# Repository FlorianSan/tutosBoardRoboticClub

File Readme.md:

# Carte tutos club Robot

Carte électronique pour apprendre les bases de l'électronique et de la programmation au nouveaux membres du club robotique.

Cette carte devrait être suffisamment compacte et pratique pour être emportée chez soi.

Sujets:

+ LEDs
+ boutons, pullups, ...
+ potentiomètre: analogique
+ PWM
+ UART
+ I2C
+ Encoder
+ Asservissement d'un moteur

Carte compatible Nucleo F411, F401RE. (et peut-être d'autres)

# Getting started

Le plus simple pour démarrer est d'installer VSCode, et l'extension PlateformIO.

Créer un projet pour la carte que vous utilisez (par exemple : ST Nucleo F401RE), avec le framwork Arduino.

Ajouter ceci au fichier `platformio.ini` pour activer l'UART6 qui va permettre de communiquer avec l'ATtiny1616 :

`build_flags = -D ENABLE_HWSERIAL6`

# Pinout

## Nucleo

| Pin | Signal    |
|-----|-----------|
|PA0  |BTN1 (B1)  |
|PA1  |BTN2 (B2)  |
|PA4  |BUZZ       |
|PA8  |Enc1A      |
|PA9  |Enc1B      |
|PA10 |Display_CLK|
|PA11 |UART6_TX   |
|PA12 |UART6_RX   |
|PA15 |MotB       |
|PB0  |POT        |
|PB1  |LED1       |
|PB4  |SERVO1     |
|PB5  |SERVO2     |
|PB6  |Enc2A      |
|PB7  |Enc2B      |
|PB8  |SCL1       |
|PB9  |SDA1       |
|PB10 |MotA       |
|PB12 |Attiny_link|
|PC4  |Display_DIO|
|PC8  |LED2       |
|PC9  |INT_TCA    |

Les jumpers JP1 et JP2 connectent respectivement une résistance de pullup et de pulldown aux signaux BTN1 et BTN2.

Afin d'utiliser les servomoteurs ou le moteur, il faut alimenter la carte par le connecteur jack DC en 12V (12V sur le connecteur central, GND sur l'extérieur), et régler le jumper JP5 de la nucleo (à côté du bouton RESET) sur "E5V".
La led D19 devrait s'allumer.

## TCA9554

| Pin | Signal  |
|-----|---------|
|P0   |D4       |
|P1   |D5       |
|P2   |D6       |
|P3   |D7       |
|P4   |D17      |
|P5   |D18      |
|P6   |SW6 (B3) |
|P7   |SW7 (B4) |

SW5 permet de régler un bit d'adresse (A0).

SW4 permet de connecter ou pas les pullups sur SDA et SCL.

La broche INT est connectée sur la broche PC9 de la nucleo.

Les broches d'adresses A1 et A2 sont connectés à GND.

datasheet : [http://www.ti.com/lit/ds/symlink/tca9554.pdf](http://www.ti.com/lit/ds/symlink/tca9554.pdf)

## Display

L'afficheur 7segments 4 digits est commandé par un TM1637.

datasheet : [https://www.mcielectronics.cl/website_MCI/static/documents/Datasheet_TM1637.pdf](https://www.mcielectronics.cl/website_MCI/static/documents/Datasheet_TM1637.pdf)

## Driver moteur

Le driver moteur est un BD62120AEFJ.

datasheet : [https://docs.rs-online.com/a300/0900766b816747fb.pdf](https://docs.rs-online.com/a300/0900766b816747fb.pdf)

## ATtiny 1616

:warning: Si vous regardez ça, vous savez ce que vous faites !

| Pin | Signal    |
|-----|-----------|
|PA0  |UPDI       |
|PA2  |Attiny_link|
|PA4  |D10        |
|PA5  |D9         |
|PA6  |D8         |
|PA7  |D16        |
|PB0  |D11        |
|PB1  |D13        |
|PB2  |UART6_RX   |
|PB3  |UART6_TX   |
|PB4  |D14        |
|PB5  |D15        |
|PC0  |D12        |
|PC1  |AtPot      |
|PC2  |AtLight    |

:warning: UART6_RX et UART6_TX sont les signaux de la nucleo, qui correspondent donc respectivement à TX et RX de l'ATtiny.

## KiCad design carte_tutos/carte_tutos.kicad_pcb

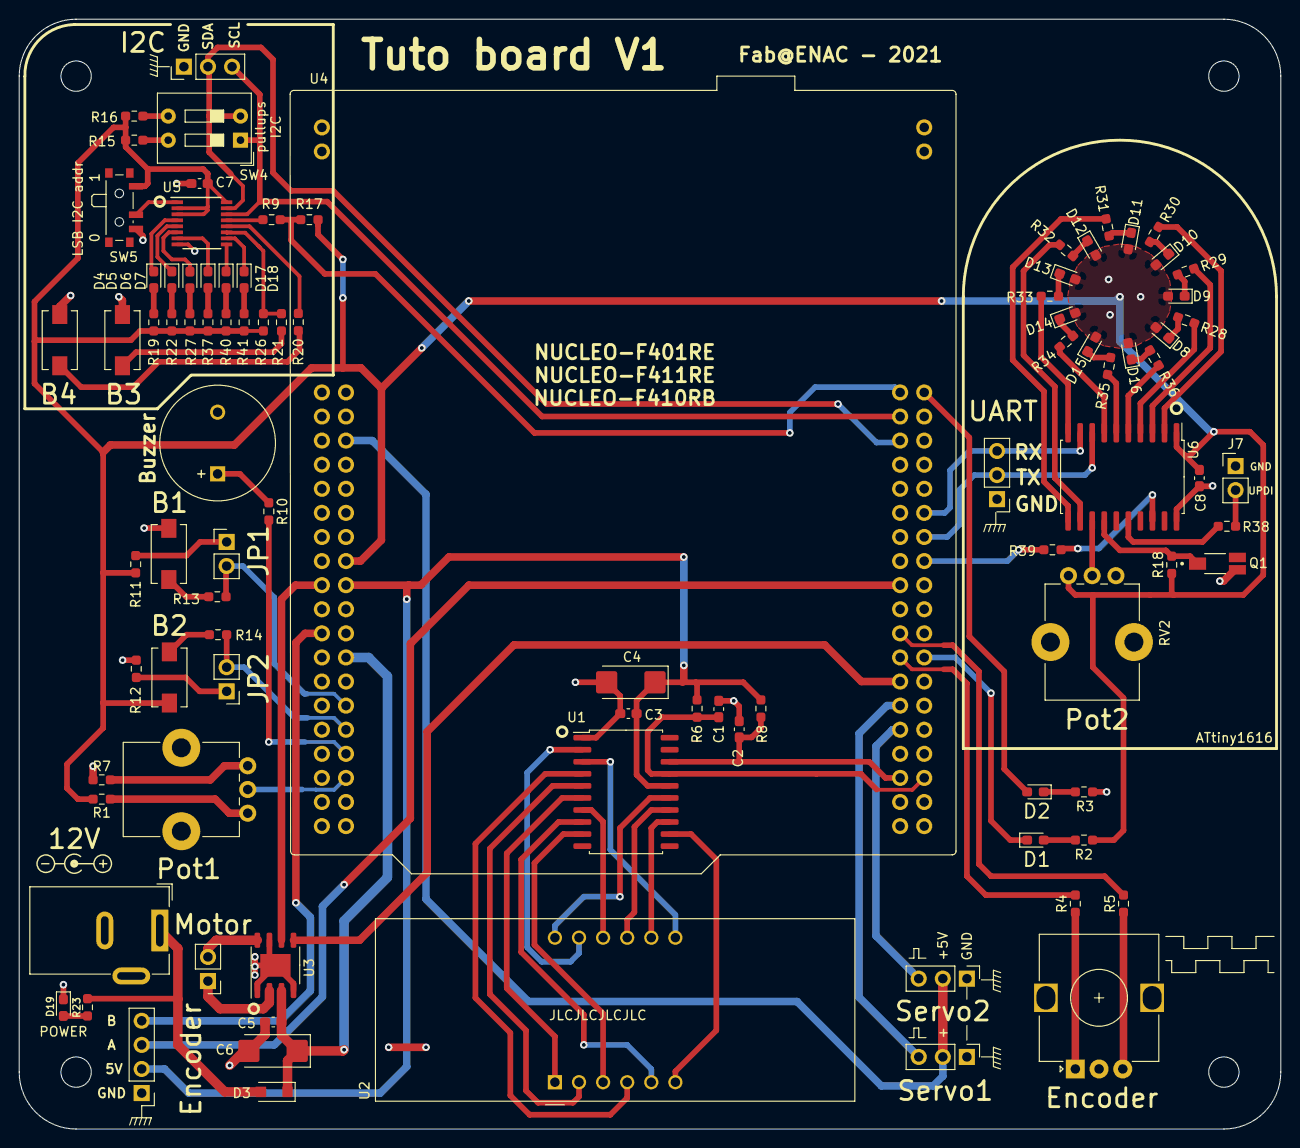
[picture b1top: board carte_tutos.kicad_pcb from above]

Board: 2 copper layers, 133.0 x 117.0 mm, 93 parts (0 on the bottom side), 97 nets.

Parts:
BZ1: Buzzer; MagneticBuzzer_ProSignal_ABT-410-RC
C1, C2: 100p; C_0603_1608Metric_Pad1.08x0.95mm_HandSolder
C3, C5, C7, C8: 100n; C_0603_1608Metric_Pad1.08x0.95mm_HandSolder
C4, C6: 100u; CP_EIA-6032-28_Kemet-C_Pad2.25x2.35mm_HandSolder
D1, D2, D4, D5, D6, D7, D8, D9, D10, D11, D12, D13, D14, D15, D16, D17, D18, D19: LED; LED_0603_1608Metric_Pad1.05x0.95mm_HandSolder
D3: D_Schottky; D_SOD-123F
J1, J2, J6, J8: Conn_01x03_Male; PinHeader_1x03_P2.54mm_Vertical
J3: Barrel_Jack; BarrelJack_Wuerth_6941xx301002
J4: Conn_01x04_Male; PinHeader_1x04_P2.54mm_Vertical
J5, J7: Conn_01x02_Male; PinHeader_1x02_P2.54mm_Vertical
JP1, JP2: Jumper; PinHeader_1x02_P2.54mm_Vertical
Q1: SFH_3410-Z; SFH_3410
R1, R4, R5, R7, R9, R13, R14, R20, R21, R39: 100; R_0603_1608Metric_Pad0.98x0.95mm_HandSolder
R2, R3, R19, R22, R27, R28, R29, R30, R31, R32, R33, R34, R35, R36, R37, R40, R41: 390; R_0603_1608Metric_Pad0.98x0.95mm_HandSolder
R6, R8, R11, R12, R17, R26: 10k; R_0603_1608Metric_Pad0.98x0.95mm_HandSolder
R10: 220; R_0603_1608Metric_Pad0.98x0.95mm_HandSolder
R15, R16: 2.2K; R_0603_1608Metric_Pad0.98x0.95mm_HandSolder
R18: 1k; R_0603_1608Metric_Pad0.98x0.95mm_HandSolder
R23: 2k; R_0603_1608Metric_Pad0.98x0.95mm_HandSolder
R38: 470; R_0603_1608Metric_Pad0.98x0.95mm_HandSolder
RV1, RV2: R_POT; Potentiometer_Bourns_PTV09A-1_Single_Vertical
SW1: Rotary_Encoder_Switch; RotaryEncoder_Alps_EC12E_Vertical_H20mm
SW2, SW3, SW6, SW7: SW_Push; SW_SPST_EVQPE1
SW4: SW_DIP_x02; SW_DIP_SPSTx02_Slide_9.78x7.26mm_W7.62mm_P2.54mm
SW5: SW_SPDT; SW_SPDT_PCM12
U1: TM1637; SOP-20_7.5x12.8mm_P1.27mm
U2: CA56-12EWA
U3: BD62120AEFJ; HTSOP-8-1EP_3.9x4.9mm_P1.27mm_EP2.4x3.2mm
U4: NUCLEO64-F411RE; ST_Morpho_Connector_64_STLink
U5: TCA9554DBQ; SSOP-16_3.9x4.9mm_P0.635mm
U6: ATtiny1616-S; SOIC-20W_7.5x12.8mm_P1.27mm

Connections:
+3V3: C7.1, C8.1, D8.2, D9.2, D10.2, D11.2, D12.2, D13.2, D14.2, D15.2, D16.2, R1.2, R2.2, R11.2, R15.1, R16.1, R17.1, R18.1, R19.1, R22.1, R26.1, R27.1, R37.1, R40.1, R41.1, RV2.1, SW3.1, SW5.1, U4.16, U5.2, U5.3, U5.16, U6.1
+5V: C3.1, C4.1, J4.2, R6.2, R8.2, U1.16, U4.18
+5VP: J1.2, J2.2, U4.6
+12V: C5.1, C6.1, D3.1, U3.3, U4.24
/AtLed1: R28.1, U6.4
/AtLed2: R29.1, U6.3
/AtLed3: R30.1, U6.2
/AtLed4: R31.1, U6.11
/AtLed5: R32.1, U6.12
/AtLed6: R33.1, U6.10
/AtLed7: R34.1, U6.7
/AtLed8: R35.1, U6.6
/AtLed9: R36.1, U6.5
/AtLight: Q1.1, R18.2, U6.14
/AtPot: RV2.2, U6.13
/GRID1: U1.15, U2.12
/GRID2: U1.14, U2.9
/GRID3: U1.13, U2.8
/GRID4: U1.12, U2.6
/UPDI: J7.2, R38.1
Attiny_link: R39.1, U4.54
BTN1: JP1.2, R13.1, U4.28
BTN2: JP2.2, R14.1, U4.30
BUZZ: R10.2, U4.32
Display_CLK: C2.2, R8.1, U1.18, U4.71
Display_DIO: C1.2, R6.1, U1.17, U4.72
Enc1A: R4.2, U4.61
Enc1B: R5.2, U4.59
Enc2A: J4.3, U4.55
Enc2B: J4.4, U4.21
GND: BZ1.2, C1.1, C2.1, C3.2, C4.2, C5.2, C6.2, C7.2, C8.2, D19.1, J1.1, J2.1, J3.2, J3.3, J4.1, J6.1, J7.1, J8.1, Q1.3, R3.2, R7.1, R12.2, RV2.3, SW1.C, SW2.1, SW5.3, SW6.2, SW7.2, U1.1, U3.1, U3.4, U3.7, U3.9, U4.8, U4.19, U4.20, U4.22, U4.47, U4.58, U4.70, U4.77, U4.78, U4.79, U4.80, U5.8, U6.20
INT_TCA: R9.2, R17.2, U4.39
LED1: D1.1, U4.62
LED2: D2.2, U4.40
MotA: U3.5, U4.63
MotB: U3.6, U4.17
unnamed: BZ1.1, R10.1
unnamed: D1.2, R2.1
unnamed: D2.1, R3.1
unnamed: D3.2, J3.1, R23.2
unnamed: D4.1, U5.4
unnamed: D4.2, R19.2
unnamed: D5.1, U5.5
unnamed: D5.2, R22.2
unnamed: D6.1, U5.6
unnamed: D6.2, R27.2
unnamed: D7.1, U5.7
unnamed: D7.2, R37.2
unnamed: D8.1, R28.2
unnamed: D9.1, R29.2
unnamed: D10.1, R30.2
unnamed: D11.1, R31.2
unnamed: D12.1, R32.2
unnamed: D13.1, R33.2
unnamed: D14.1, R34.2
unnamed: D15.1, R35.2
unnamed: D16.1, R36.2
unnamed: D17.1, U5.9
unnamed: D17.2, R40.2
unnamed: D18.1, U5.10
unnamed: D18.2, R41.2
unnamed: D19.2, R23.1
unnamed: J5.1, U3.2
unnamed: J5.2, U3.8
unnamed: JP1.1, R11.1
unnamed: JP2.1, R12.1
unnamed: R1.1, RV1.3
unnamed: R4.1, SW1.A
unnamed: R5.1, SW1.B
unnamed: R7.2, RV1.1
unnamed: R9.1, U5.13
unnamed: R13.2, SW2.2
unnamed: R14.2, SW3.2
unnamed: R15.2, SW4.4
unnamed: R16.2, SW4.3
unnamed: R20.1, SW7.1
unnamed: R20.2, U5.12
unnamed: R21.1, SW6.1
unnamed: R21.2, R26.2, U5.11
unnamed: R38.2, U6.16
unnamed: R39.2, U6.18
unnamed: SW5.2, U5.1
unnamed: U1.2, U2.11
unnamed: U1.3, U2.7
unnamed: U1.4, U2.4
unnamed: U1.5, U2.2
unnamed: U1.6, U2.1
unnamed: U1.7, U2.10
unnamed: U1.8, U2.5
unnamed: U1.9, U2.3
POT: RV1.2, U4.34
SCL1: J6.3, SW4.1, U4.41, U5.14
SDA1: J6.2, SW4.2, U4.43, U5.15
SERVO1: J1.3, U4.65
SERVO2: J2.3, U4.67
UART6_RX: J8.3, U4.50, U6.9
UART6_TX: J8.2, U4.52, U6.8

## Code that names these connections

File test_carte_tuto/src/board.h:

#pragma once

#include <Arduino.h>

#define TCA_ADDR_LSB 1

#define BTN1 PA0
#define BTN2 PA1
#define BUZZ PA4
#define ENC1A PA8
#define ENC1B PA9
#define DISPLAY_CLK PA10
#define UART6_TX PA11
#define UART6_RX PA12
#define MOTB PA15
#define POT PB0
#define LED1 PB1
#define SERVO1 PB4
#define SERVO2 PB5
#define ENC2A PB6
#define ENC2B PB7
#define SCL1 PB8
#define SDA1 PB9
#define MOTA PB10
#define ATTINY_LINK PB12
#define DISPLAY_DIO PC4
#define LED2 PC8
#define INT_TCA PC9


#define TCA_ADDR (0x26 + TCA_ADDR_LSB)
#define TCA_INPUT_PORT 0x00
#define TCA_OUTPUT_PORT 0x01
#define TCA_POL_INV 0x02
#define TCA_CONFIG 0x03

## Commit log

2021-07-23 Initial commit.
2021-07-23 Add readme.
2021-07-23 Add ATtiny1616.
2021-07-25 Add project libs, schematic almost done.
2021-07-25 Fix ERC warnings.
2021-07-25 Associate some footprints.
2021-07-25 Add cubeMx config.
2021-07-25 Add decoupling capacitor, and associate footprints
2021-07-25 More footprint assignments.
2021-07-25 Remove touch sensors.
2021-07-25 Add BOM
2021-07-25 Barrel jack & cleaning.
2021-07-25 Fix nucleo footprint.
2021-07-25 begin PCB
2021-07-26 More layout, and small schematic edits.
2021-07-26 Layout almost complete.
2021-07-26 Finish layout.
2021-07-26 silk
2021-07-26 Nucleo: reduce courtyard.
2021-07-27 More silk, and add power led.
2021-07-27 Update cubMx, Update BOM
2021-07-27 Update Readme.
2021-07-27 More docs.
2021-07-27 Improve Silk.
2021-07-28 First pages commit
2021-07-29 Add mdBooks for the tuto.
2021-07-29 deploy: eb3ac33ed96700378bfb3aeebd45245ef76c4c21
2021-07-30 Fix unrouted track.
2021-09-14 Add Attiny project.
2021-09-14 Add nucleo test code.
2021-09-14 Starts comm lib
2021-09-14 rename file
2021-09-14 begin protocol.
2021-09-15 [ATtiny] Implement most of the protocol and behavior.
2021-09-15 Adds atttiny communication support
2021-09-15 [ATtiny] Fix some errors.
2021-09-15 [ATtiny] Improve registers operations.
2021-09-15 [ATtiny] Make continuous frequency configurable.
2021-09-16 [Nucleo] Dirty little test.
2021-09-17 [Attiny] Nicer register initialization.
2021-09-17 [Nucleo] Stealth startup trick.
2021-09-17 Update doc.
2021-09-17 deploy: 97e3b31578ef9230b60cd6c6da5c6c841c17ced5
2022-06-27 WIP? Will be cleaned up!
2023-01-20 Begin chibiOs example.
2023-01-20 Improve chibiOS build.
2023-01-20 [chibios] Move source files to dedicated directory.
2023-01-23 [ChibiOS] Improve board.cfg
2023-01-23 [ChibiOS] set vscode includePath.
2023-01-23 Add schematics.
2023-01-24 test
2023-01-24 [ChibiOS] Improve example.
2023-01-25 [ChibiOS] Add I2C.
2024-12-24 Update chibios
2024-12-24 Toggle led with rust
